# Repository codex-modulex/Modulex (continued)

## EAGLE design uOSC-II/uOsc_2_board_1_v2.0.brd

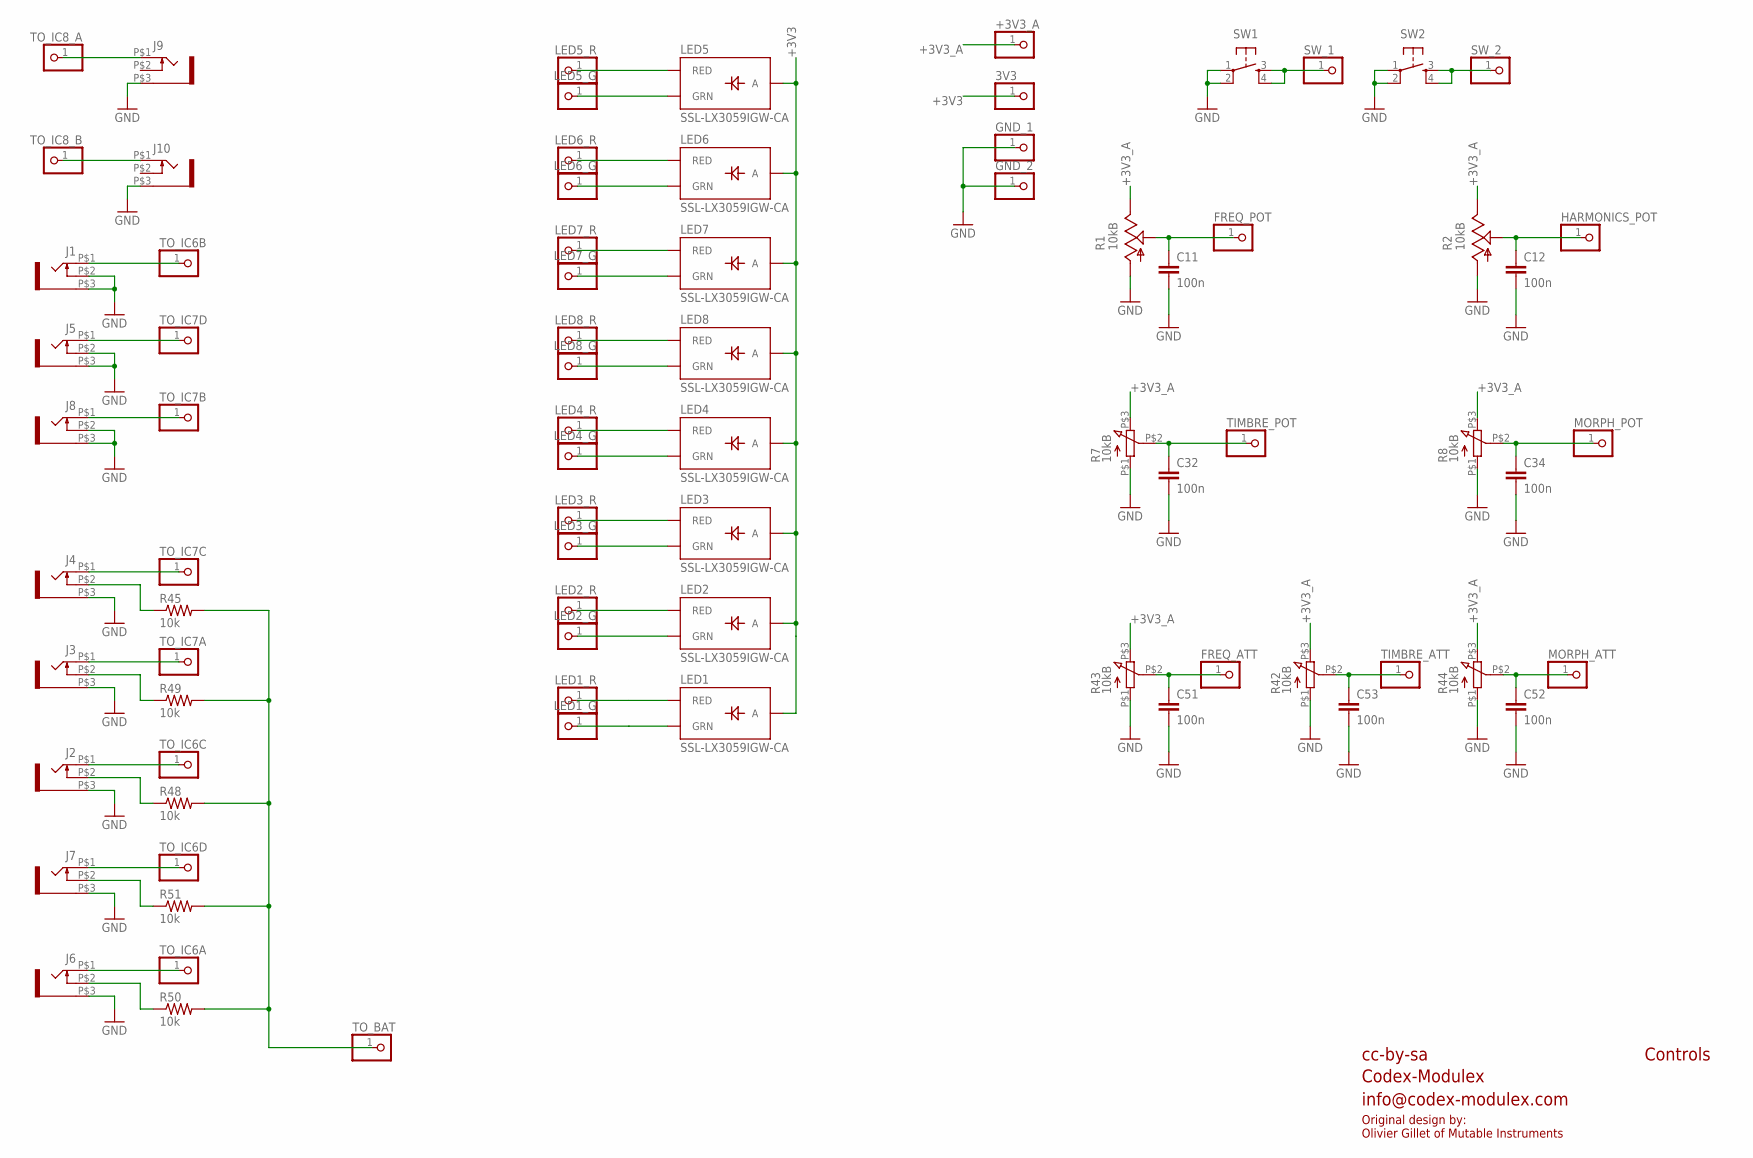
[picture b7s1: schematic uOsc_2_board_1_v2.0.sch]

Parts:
3V3: PARTS_AMAN_PINHD-1X1; PARTS_AMAN_1X01
+3V3_A: PARTS_AMAN_PINHD-1X1; PARTS_AMAN_1X01
C11, C12, C32, C34, C51, C52, C53: 100n; PARTS_AMAN_RESISTOR_0603
FREQ_ATT: PARTS_AMAN_PINHD-1X1; PARTS_AMAN_1X01
FREQ_POT: PARTS_AMAN_PINHD-1X1; PARTS_AMAN_1X01
GND_1, GND_2: PARTS_AMAN_PINHD-1X1; PARTS_AMAN_1X01
HARMONICS_POT: PARTS_AMAN_PINHD-1X1; PARTS_AMAN_1X01
J1, J2, J3, J4, J5, J6, J7, J8, J9, J10: WQP-PJ301M-12_JACK
LED1, LED2, LED3, LED4, LED5, LED6, LED7, LED8: SSL-LX3059IGW-CA; LED-BICOLOR-THROUGHHOLE-LUMEX
LED1_G, LED1_R, LED2_G, LED2_R, LED3_G, LED3_R, LED4_G, LED4_R, LED5_G, LED5_R, LED6_G, LED6_R, LED7_G, LED7_R, LED8_G, LED8_R: PARTS_AMAN_PINHD-1X1; PARTS_AMAN_1X01
MORPH_ATT: PARTS_AMAN_PINHD-1X1; PARTS_AMAN_1X01
MORPH_POT: PARTS_AMAN_PINHD-1X1; PARTS_AMAN_1X01
R1, R2: 10kB; ALPS_POT_VERTICAL_PS
R7, R8, R42, R43, R44: 10kB; INSTRUO_Q-POT2
R45, R48, R49, R50, R51: 10k; PARTS_AMAN_RESISTOR_0603
SW1, SW2: TAC_SWITCHPTH; TACTILE-PTH
SW_1, SW_2: PARTS_AMAN_PINHD-1X1; PARTS_AMAN_1X01
TIMBRE_ATT: PARTS_AMAN_PINHD-1X1; PARTS_AMAN_1X01
TIMBRE_POT: PARTS_AMAN_PINHD-1X1; PARTS_AMAN_1X01
TO_BAT: PARTS_AMAN_PINHD-1X1; PARTS_AMAN_1X01
TO_IC6A, TO_IC6B, TO_IC6C, TO_IC6D, TO_IC7A, TO_IC7B, TO_IC7C, TO_IC7D, TO_IC8_A, TO_IC8_B: PARTS_AMAN_PINHD-1X1; PARTS_AMAN_1X01

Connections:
+3V3: 3V3.1, LED1.A, LED2.A, LED3.A, LED4.A, LED5.A, LED6.A, LED7.A, LED8.A
+3V3_A: +3V3_A.1, R1.P$1 (E), R2.P$1 (E), R7.P$3 (3), R8.P$3 (3), R42.P$3 (3), R43.P$3 (3), R44.P$3 (3)
FREQ_ATT: C51.1, FREQ_ATT.1, R43.P$2 (2)
FREQ_POT: C11.1, FREQ_POT.1, R1.P$2 (S)
GND: C11.2, C12.2, C32.2, C34.2, C51.2, C52.2, C53.2, GND_1.1, GND_2.1, J1.P$2 (3), J1.P$3 (1), J2.P$3 (1), J3.P$3 (1), J4.P$3 (1), J5.P$2 (3), J5.P$3 (1), J6.P$3 (1), J7.P$3 (1), J8.P$2 (3), J8.P$3 (1), J9.P$3 (1), J10.P$3 (1), R1.P$3 (A), R2.P$3 (A), R7.P$1 (1), R8.P$1 (1), R42.P$1 (1), R43.P$1 (1), R44.P$1 (1), SW1.1, SW1.2, SW2.1, SW2.2
HARMONICS_POT: C12.1, HARMONICS_POT.1, R2.P$2 (S)
MORPH_ATT: C52.1, MORPH_ATT.1, R44.P$2 (2)
MORPH_POT: C34.1, MORPH_POT.1, R8.P$2 (2)
unnamed: LED1.GREEN_C (GRN), LED1_G.1
unnamed: LED2.GREEN_C (GRN), LED2_G.1
unnamed: LED2.RED_C (RED), LED2_R.1
unnamed: J4.P$1 (2), TO_IC7C.1
unnamed: LED1.RED_C (RED), LED1_R.1
unnamed: LED3.RED_C (RED), LED3_R.1
unnamed: LED3.GREEN_C (GRN), LED3_G.1
unnamed: LED4.RED_C (RED), LED4_R.1
unnamed: LED4.GREEN_C (GRN), LED4_G.1
unnamed: LED8.RED_C (RED), LED8_R.1
unnamed: LED8.GREEN_C (GRN), LED8_G.1
unnamed: LED7.RED_C (RED), LED7_R.1
unnamed: LED7.GREEN_C (GRN), LED7_G.1
unnamed: J1.P$1 (2), TO_IC6B.1
unnamed: LED6.RED_C (RED), LED6_R.1
unnamed: LED6.GREEN_C (GRN), LED6_G.1
unnamed: LED5.RED_C (RED), LED5_R.1
unnamed: LED5.GREEN_C (GRN), LED5_G.1
unnamed: J9.P$1 (2), TO_IC8_A.1
unnamed: J10.P$1 (2), TO_IC8_B.1
unnamed: J5.P$1 (2), TO_IC7D.1
unnamed: J8.P$1 (2), TO_IC7B.1
unnamed: J3.P$1 (2), TO_IC7A.1
unnamed: J2.P$1 (2), TO_IC6C.1
unnamed: J7.P$1 (2), TO_IC6D.1
unnamed: J6.P$1 (2), TO_IC6A.1
unnamed: J4.P$2 (3), R45.1
unnamed: J3.P$2 (3), R49.1
unnamed: J2.P$2 (3), R48.1
unnamed: J7.P$2 (3), R51.1
unnamed: J6.P$2 (3), R50.1
unnamed: R45.2, R48.2, R49.2, R50.2, R51.2, TO_BAT.1
SW_1: SW1.3, SW1.4, SW_1.1
SW_2: SW2.3, SW2.4, SW_2.1
TIMBRE_ATT: C53.1, R42.P$2 (2), TIMBRE_ATT.1
TIMBRE_POT: C32.1, R7.P$2 (2), TIMBRE_POT.1

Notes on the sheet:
cc-by-sa
Codex-Modulex
info@codex-modulex.com
Controls
Original design by: Olivier Gillet of Mutable Instruments

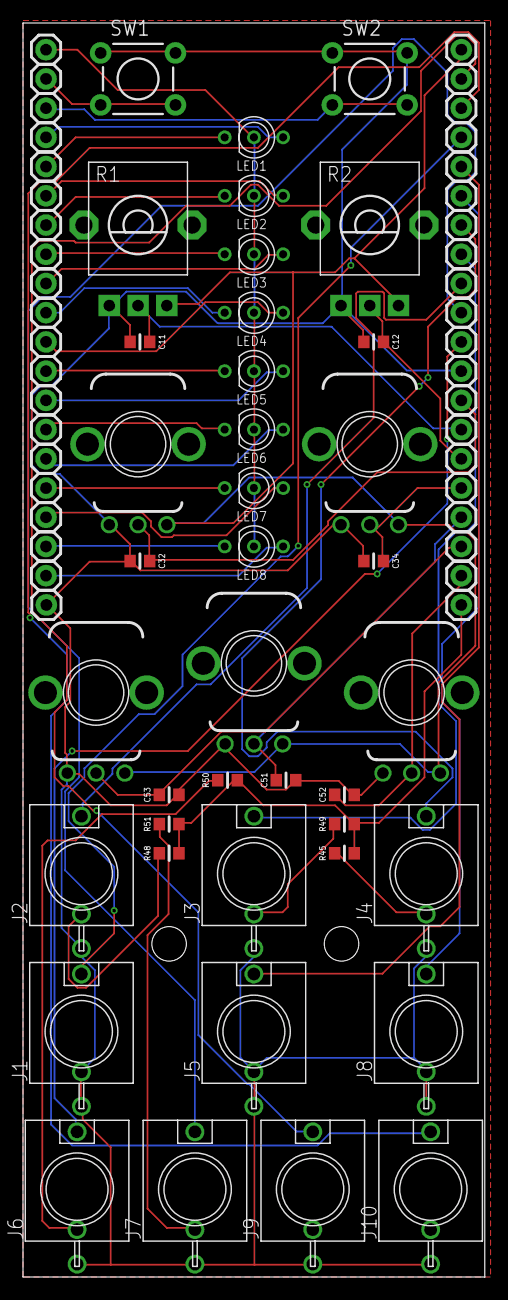
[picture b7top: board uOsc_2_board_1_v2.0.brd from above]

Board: 2 copper layers, 40.1 x 109.0 mm, 79 parts (0 on the bottom side), 44 nets.

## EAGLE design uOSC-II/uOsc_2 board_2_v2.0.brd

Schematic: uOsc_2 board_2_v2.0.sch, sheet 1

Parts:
C9, C19, C24, C25: 1u; PARTS_AMAN_RESISTOR_0603
C10, C15, C20, C23, C26: 100n; PARTS_AMAN_RESISTOR_0603
C14, C21: 20p; PARTS_AMAN_RESISTOR_0603
IC4: STM32F373CCT6; LQFP48
JP5: M02PTH; 1X02
JP6: M04PTH; 1X04
Q1: 8MHz; CTS406
R4: 10k; PARTS_AMAN_RESISTOR_0603
R5, R6, R9, R10: 100; PARTS_AMAN_RESISTOR_0603

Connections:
+3V3: C9.1, C10.1, C25.1, C26.1, IC4.1 (VBAT), IC4.17 (VDD_2), IC4.48 (VDD_1), R4.1; also elsewhere on the board
+3V3_A: C19.1, C20.1, C23.1, C24.1, IC4.9 (VDDA), IC4.24 (VDDSD), IC4.25 (VREFSD+); also elsewhere on the board
ADC_FM: IC4.22 (PE9/SDADC1_AIN7P/SDADC1_AIN8M/SDADC2_AI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); also elsewhere on the board
ADC_GATE: IC4.21 (PE8/SDADC1_AIN8P/SDADC2_AIN8P); also elsewhere on the board
ADC_HARMONICS: IC4.28 (PD8/SPI2_SCK/I2S2_CK/USART3_TX/SDADC3_A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); also elsewhere on the board
ADC_MODEL: IC4.19 (PB1/TIM3_CH4/ADC_IN9/SDADC1_AIN5P/SDADC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); also elsewhere on the board
ADC_MORPH: IC4.27 (PB15/SPI2_MOSI/I2S2_SD/SDADC3_AIN7P/SDA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); also elsewhere on the board
ADC_TIMBRE: IC4.20 (PB2/SDADC1_AIN4P/SDADC2_AIN6P); also elsewhere on the board
ADC_TRIG: IC4.18 (PB0/SPI1_MOSI/I2S1_SD/TIM3_CH3/ADC_IN8/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); also elsewhere on the board
ADC_V_OCT: IC4.26 (PB14/SPI2_MISO/I2S2_MCK/USART3_RTS/SDAD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); also elsewhere on the board
DAC_BCK: IC4.29 (PA8/SPI2_SCK/I2S2_CK/I2C2_SMBA/USART1_C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); also elsewhere on the board
DAC_DIN: IC4.31 (PA10/SPI2_MOSI/I2S2_SD/I2C2_SDA/USART1_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); also elsewhere on the board
DAC_LRCK: IC4.32 (PA11/SPI2_NSS/I2S2_WS/SPI1_NSS/I2S1_WS/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); also elsewhere on the board
FREQ_ATT: IC4.15 (PA5/SPI1_SCK/I2S1_CK/TIM2_CH1/ADC_IN5/D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); also elsewhere on the board
FREQ_POT: IC4.10 (PA0/USART2_CTS/TIM2_CH1/TIM5_CH1/ADC_IN0); also elsewhere on the board
GND: C9.2, C10.2, C14.1, C15.2, C19.2, C20.2, C21.1, C23.2, C24.2, C25.2, C26.2, IC4.8 (VSSA), IC4.23 (VSSSD/VREFSD-), IC4.44 (BOOT0), IC4.47 (VSS_1), JP6.1, Q1.2 (LID1), Q1.4 (LID2); also elsewhere on the board
HARMONICS_POT: IC4.12 (PA2/SPI3_MISO/I2S3_MCK/USART2_TX/TIM2_C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); also elsewhere on the board
LEDS_SCK: IC4.33 (PA12/SPI1_SCK/I2S1_CK/USART1_RTS/CAN_TX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); also elsewhere on the board
LEDS_SIN: IC4.35 (PF6/SPI1_MOSI/I2S1_SD/USART3_RTS/TIM4_C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); also elsewhere on the board
LEDS_SS: IC4.36 (PF7/I2C2_SDA/USART2_CK); also elsewhere on the board
MORPH_ATT: IC4.14 (PA4/SPI1_NSS/I2S1_WS/SPI3_NSS/I2S3_WS/U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); also elsewhere on the board
MORPH_POT: IC4.11 (PA1/SPI3_SCK/I2S3_CK/USART2_RTS/TIM2_CH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); also elsewhere on the board
unnamed: IC4.5 (PF0/OSC_IN/I2C2_SDA), R5.1
unnamed: IC4.6 (PF1/OSC_OUT/I2C2_SCL), R6.1
unnamed: C14.2, Q1.3 (2), R5.2
unnamed: JP5.2, R10.1
unnamed: C21.2, Q1.1, R6.2
unnamed: JP5.1, R9.1
NORMALIZATION_PROBE: IC4.30 (PA9/SPI_MISO/I2S2_MCK/I2C2_SCL/USART1_T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); also elsewhere on the board
RESET: C15.1, IC4.7 (NRST), JP6.4, R4.2
RX: IC4.46 (PB9/SPI2_NSS/I2S2_WS/I2C1_SDA/USART3_RX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), R9.2
SWCLK: IC4.37 (PA14/I2C1_SDA/JTCK-SWCLK), JP6.3
SWDIO: IC4.34 (PA13/SPI1_MISO/I2S1_MCK/USART3_CTS/TIM4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), JP6.2
SW_1: IC4.43 (PB7/I2C1_SDA/USART1_RX/TIM4_CH2); also elsewhere on the board
SW_2: IC4.42 (PB6/I2C1_SCL/USART1_TX/TIM4_CH1); also elsewhere on the board
TIMBRE_ATT: IC4.16 (PA6/SPI1_MISO/I2S1_MCK/TIM3_CH1/ADC_IN6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); also elsewhere on the board
TIMBRE_POT: IC4.13 (PA3/SPI3_MOSI/I2S3_SD/USART2_RX/TIM2_CH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); also elsewhere on the board
TX: IC4.45 (PB8/SPI2_SCK/I2S2_CK/I2C1_SCL/USART3_TX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), R10.2

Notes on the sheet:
cc-by-sa
Codex-Modulex
info@codex-modulex.com
MCU
Factory testing interface
Original design by: Olivier Gillet of Mutable Instruments

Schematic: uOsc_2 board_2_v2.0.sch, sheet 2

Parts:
3V3: PARTS_AMAN_PINHD-1X1; PARTS_AMAN_1X01
+3V3_A: PARTS_AMAN_PINHD-1X1; PARTS_AMAN_1X01
C7: 10u; PANASONIC_A
C8: 100n; PARTS_AMAN_RESISTOR_0603
FREQ_ATT: PARTS_AMAN_PINHD-1X1; PARTS_AMAN_1X01
FREQ_POT: PARTS_AMAN_PINHD-1X1; PARTS_AMAN_1X01
GND_1: GND_1; PARTS_AMAN_1X01
GND_2: GND_2; PARTS_AMAN_1X01
HARMONICS_POT: PARTS_AMAN_PINHD-1X1; PARTS_AMAN_1X01
IC2: TLC59281DBQ; TSSOP24_0635
L4: WE-CBF_0603; 0603
LED1_G, LED1_R, LED2_G, LED2_R, LED3_G, LED3_R, LED4_G, LED4_R, LED5_G, LED5_R, LED6_G, LED6_R, LED7_G, LED7_R, LED8_G, LED8_R: PARTS_AMAN_PINHD-1X1; PARTS_AMAN_1X01
MORPH_ATT: PARTS_AMAN_PINHD-1X1; PARTS_AMAN_1X01
MORPH_POT: PARTS_AMAN_PINHD-1X1; PARTS_AMAN_1X01
R3: 10k; PARTS_AMAN_RESISTOR_0603
SW1, SW2: PARTS_AMAN_PINHD-1X1; PARTS_AMAN_1X01
TIMBRE_ATT: PARTS_AMAN_PINHD-1X1; PARTS_AMAN_1X01
TIMBRE_POT: PARTS_AMAN_PINHD-1X1; PARTS_AMAN_1X01

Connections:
+3V3: 3V3.1, L4.2; also elsewhere on the board
+3V3_A: +3V3_A.1; also elsewhere on the board
FREQ_ATT: FREQ_ATT.1; also elsewhere on the board
FREQ_POT: FREQ_POT.1; also elsewhere on the board
GND: C7.-, C8.2, GND_1.1, GND_2.1, IC2.1 (GND), IC2.21 (BLANK), R3.2; also elsewhere on the board
HARMONICS_POT: HARMONICS_POT.1; also elsewhere on the board
LEDS_SCK: IC2.3 (SCLK); also elsewhere on the board
LEDS_SIN: IC2.2 (SIN); also elsewhere on the board
LEDS_SS: IC2.4 (LAT); also elsewhere on the board
MORPH_ATT: MORPH_ATT.1; also elsewhere on the board
MORPH_POT: MORPH_POT.1; also elsewhere on the board
unnamed: IC2.12 (OUT7), LED8_G.1
unnamed: IC2.11 (OUT6), LED8_R.1
unnamed: IC2.10 (OUT5), LED7_G.1
unnamed: IC2.9 (OUT4), LED7_R.1
unnamed: IC2.8 (OUT3), LED6_G.1
unnamed: IC2.13 (OUT8), LED4_R.1
unnamed: IC2.7 (OUT2), LED6_R.1
unnamed: IC2.14 (OUT9), LED4_G.1
unnamed: IC2.6 (OUT1), LED5_G.1
unnamed: IC2.15 (OUT10), LED3_R.1
unnamed: IC2.16 (OUT11), LED3_G.1
unnamed: IC2.17 (OUT12), LED2_R.1
unnamed: IC2.18 (OUT13), LED2_G.1
unnamed: IC2.19 (OUT14), LED1_R.1
unnamed: IC2.5 (OUT0), LED5_R.1
unnamed: IC2.20 (OUT15), LED1_G.1
unnamed: C7.+, C8.1, IC2.24 (VCC), L4.1
unnamed: IC2.23 (IREF), R3.1
SW_1: SW1.1; also elsewhere on the board
SW_2: SW2.1; also elsewhere on the board
TIMBRE_ATT: TIMBRE_ATT.1; also elsewhere on the board
TIMBRE_POT: TIMBRE_POT.1; also elsewhere on the board

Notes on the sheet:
cc-by-sa
Codex-Modulex
info@codex-modulex.com
Controls
Original design by: Olivier Gillet of Mutable Instruments

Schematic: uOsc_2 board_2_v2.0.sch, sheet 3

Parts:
C36, C44: 100n; PARTS_AMAN_RESISTOR_0603
C38, C46: 100p; PARTS_AMAN_RESISTOR_0603
C39, C40, C41, C47, C48, C49: 1.0n; PARTS_AMAN_RESISTOR_0603
C54, C55, C56, C57, C58, C59, C60, C61: ESD; PARTS_AMAN_RESISTOR_0603
D3: BAT54S; SOT23
IC6, IC7: MCP6004; TSSOP14_065
R13, R14, R15, R24, R38, R39, R40, R41: 100k; PARTS_AMAN_RESISTOR_0603
R17: 56k; PARTS_AMAN_RESISTOR_0603
R18, R20, R31, R34: 33k; PARTS_AMAN_RESISTOR_0603
R19, R32, R35: 20k; PARTS_AMAN_RESISTOR_0603
R23, R33, R36: 120k; PARTS_AMAN_RESISTOR_0603
R25, R27, R30: 200k; PARTS_AMAN_RESISTOR_0603
R26: 110k; PARTS_AMAN_RESISTOR_0603
R29: 140k; PARTS_AMAN_RESISTOR_0603
TO_BAT: PARTS_AMAN_PINHD-1X1; PARTS_AMAN_1X01
TO_IC6A, TO_IC6B, TO_IC6C, TO_IC6D, TO_IC7A, TO_IC7B, TO_IC7C, TO_IC7D: PARTS_AMAN_PINHD-1X1; PARTS_AMAN_1X01

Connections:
+3V3: D3.2 (C); also elsewhere on the board
+3V3_A: C36.1, C44.1, IC6.4 (V+), IC7.4 (V+); also elsewhere on the board
ADC_FM: C40.2, IC7.1 (OUT), R19.1; also elsewhere on the board
ADC_GATE: C39.2, IC6.14 (OUT), R18.1; also elsewhere on the board
ADC_HARMONICS: C41.2, IC7.14 (OUT), R20.1; also elsewhere on the board
ADC_MODEL: C46.2, IC6.7 (OUT), R31.1; also elsewhere on the board
ADC_MORPH: C49.2, IC7.8 (OUT), R35.1; also elsewhere on the board
ADC_TIMBRE: C47.2, IC6.8 (OUT), R32.1; also elsewhere on the board
ADC_TRIG: C38.2, IC6.1 (OUT), R17.1; also elsewhere on the board
ADC_V_OCT: C48.2, IC7.7 (OUT), R34.1; also elsewhere on the board
AREF_-10: R23.2, R25.2, R26.2, R27.2, R29.2, R30.2, R33.2, R36.2; also elsewhere on the board
FM_IN: C57.1, R15.2, TO_IC7A.1
GATE_IN: C61.1, R14.2, TO_IC6D.1
GATE_IN1: C59.1, R24.2, TO_IC6A.1
GND: C36.2, C44.2, C54.2, C55.2, C56.2, C57.2, C58.2, C59.2, C60.2, C61.2, D3.1 (A), IC6.3 (+IN), IC6.5 (+IN), IC6.10 (+IN), IC6.11 (V-), IC6.12 (+IN), IC7.3 (+IN), IC7.5 (+IN), IC7.10 (+IN), IC7.11 (V-), IC7.12 (+IN); also elsewhere on the board
HARMONICS_IN: C58.1, R13.2, TO_IC7D.1
MODEL_IN: C55.1, R40.2, TO_IC6B.1
MORPH_IN: C54.1, R39.2, TO_IC7C.1
unnamed: C38.1, IC6.2 (-IN), R17.2, R24.1, R25.1
unnamed: C39.1, IC6.13 (-IN), R14.1, R18.2, R26.1
unnamed: C48.1, IC7.6 (-IN), R29.1, R34.2, R38.1
unnamed: C56.1, R41.2, TO_IC6C.1
unnamed: C49.1, IC7.9 (-IN), R35.2, R36.1, R39.1
unnamed: C40.1, IC7.2 (-IN), R15.1, R19.2, R23.1
unnamed: C46.1, IC6.6 (-IN), R30.1, R31.2, R40.1
unnamed: C47.1, IC6.9 (-IN), R32.2, R33.1, R41.1
unnamed: C41.1, IC7.13 (-IN), R13.1, R20.2, R27.1
NORMALIZATION_PROBE: D3.3 (AC), TO_BAT.1; also elsewhere on the board
V_OCT_IN: C60.1, R38.2, TO_IC7B.1

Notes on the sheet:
cc-by-sa
Codex-Modulex
info@codex-modulex.com
CV inputs
-3.0V to 7.0V
-8.0V to 8.0V
-5.0V to 5.0V
-0.8V to 8.0V
-0.8V to 5.0V
Optional ESD protection:
1.0nF capacitor
or:
Ceradiode (eg TDK B72500D160H60, AEM ES0603V014CT)
Original design by: Olivier Gillet of Mutable Instruments

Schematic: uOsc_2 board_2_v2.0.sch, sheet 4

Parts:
C16, C30: 10u; PANASONIC_A
C17, C18, C27, C28, C37, C45: 100n; PARTS_AMAN_RESISTOR_0603
C29, C31: 2.2u; C0805
C33, C35: 1.0n; PARTS_AMAN_RESISTOR_0603
C42, C43: 100p; PARTS_AMAN_RESISTOR_0603
IC5: PCM5100APW; SSOP20
IC8: TL072PW; TSSOP08
R11, R12: 2.2k; PARTS_AMAN_RESISTOR_0603
R16, R21: 10k; PARTS_AMAN_RESISTOR_0603
R22, R28: 33k; PARTS_AMAN_RESISTOR_0603
R46, R47: 1.0k; PARTS_AMAN_RESISTOR_0603
TO_IC8A, TO_IC8B: PARTS_AMAN_PINHD-1X1; PARTS_AMAN_1X01

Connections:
+3V3: C16.+, C17.1, IC5.11 (FLT), IC5.17 (XSMT), IC5.20 (DVDD); also elsewhere on the board
+3V3_A: C27.1, C28.1, C30.+, IC5.1 (CPVDD), IC5.8 (AVDD); also elsewhere on the board
DAC_BCK: IC5.13 (BCK); also elsewhere on the board
DAC_DIN: IC5.14 (DIN); also elsewhere on the board
DAC_LRCK: IC5.15 (LRCK); also elsewhere on the board
GND: C16.-, C17.2, C18.2, C27.2, C28.2, C30.-, C31.2, C33.2, C35.2, C37.2, C45.1, IC5.3 (CPGND), IC5.9 (AGND), IC5.10 (DEMP), IC5.12 (SCK), IC5.16 (FMT), IC5.19 (DGND), IC8.3 (+IN), IC8.5 (+IN); also elsewhere on the board
unnamed: C29.1, IC5.2 (CAPP)
unnamed: C29.2, IC5.4 (CAPM)
unnamed: IC5.6 (OUTL), R11.2
unnamed: C33.1, R11.1, R21.2
unnamed: C35.1, R12.1, R16.2
unnamed: C31.1, IC5.5 (VNEG)
unnamed: C18.1, IC5.18 (LDOO)
unnamed: IC5.7 (OUTR), R12.2
unnamed: C43.1, IC8.6 (-IN), R16.1, R28.2
unnamed: C43.2, IC8.7 (OUT), R28.1, R47.2
unnamed: C42.1, IC8.2 (-IN), R21.1, R22.2
unnamed: C42.2, IC8.1 (OUT), R22.1, R46.2
unnamed: R46.1, TO_IC8A.1
unnamed: R47.1, TO_IC8B.1
VCC: C37.1, IC8.8 (V+); also elsewhere on the board
VEE: C45.2, IC8.4 (V-); also elsewhere on the board

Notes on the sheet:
cc-by-sa
Codex-Modulex
info@codex-modulex.com
DAC and outputs
Original design by: Olivier Gillet of Mutable Instruments

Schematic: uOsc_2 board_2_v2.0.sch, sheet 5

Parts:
C1, C2, C13: 22u; C1206
C3, C22: 10u; PANASONIC_A
C4, C5: 22u; PANASONIC_B
C6: 100n; PARTS_AMAN_RESISTOR_0603
C50: 1u; PARTS_AMAN_RESISTOR_0603
D1, D2: 1N5819HW; SOD123
IC1: R-78E3.3-0.5; WE78
IC3: LD2981ABU33; SOT89
IC9: LM4040B10; DBZ_R-PDSO-G3
JP8: M05X2SHD; 2X5-SHROUDED
L1: 33u; L2012C
L2, L3, L5: WE-CBF_0603; 0603
R37: 2.2k; PARTS_AMAN_RESISTOR_0603

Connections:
+3V3: C3.+, C6.1, IC1.3 (VO); also elsewhere on the board
+3V3_A: C22.+, IC3.1 (VO); also elsewhere on the board
AREF_-10: C50.1, IC9.2 (A), R37.2; also elsewhere on the board
GND: C1.2, C2.2, C3.-, C4.-, C5.+, C6.2, C13.2, C22.-, C50.2, IC1.2 (GND), IC3.2 (GND), IC9.1 (C), JP8.3, JP8.4, JP8.5, JP8.6, JP8.7, JP8.8; also elsewhere on the board
unnamed: C1.1, IC1.1 (VI), L1.2
unnamed: D2.A, L3.2
unnamed: C2.1, D1.C, L1.1, L2.2, L5.2
unnamed: C13.1, IC3.3 (VI), L5.1
unnamed: D1.A, JP8.9, JP8.10
unnamed: D2.C, JP8.1, JP8.2
VCC: C4.+, L2.1; also elsewhere on the board
VEE: C5.-, L3.1, R37.1; also elsewhere on the board

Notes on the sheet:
cc-by-sa
Codex-Modulex
info@codex-modulex.com
Power
0.56mA needed
Wurth 742792664
0.68mA delivered
Original design by: Olivier Gillet of Mutable Instruments

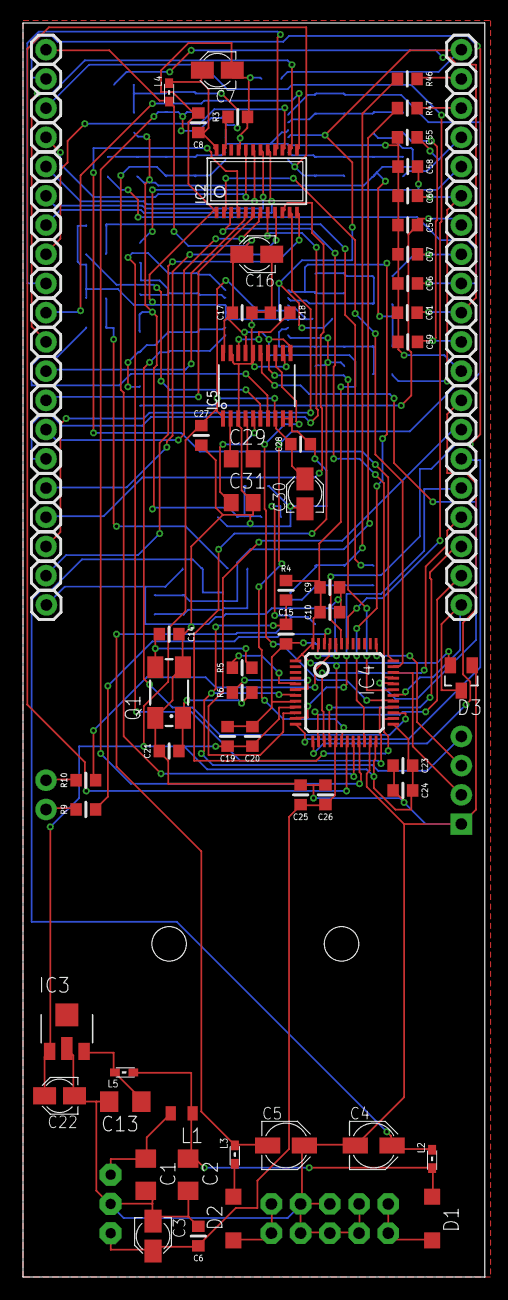
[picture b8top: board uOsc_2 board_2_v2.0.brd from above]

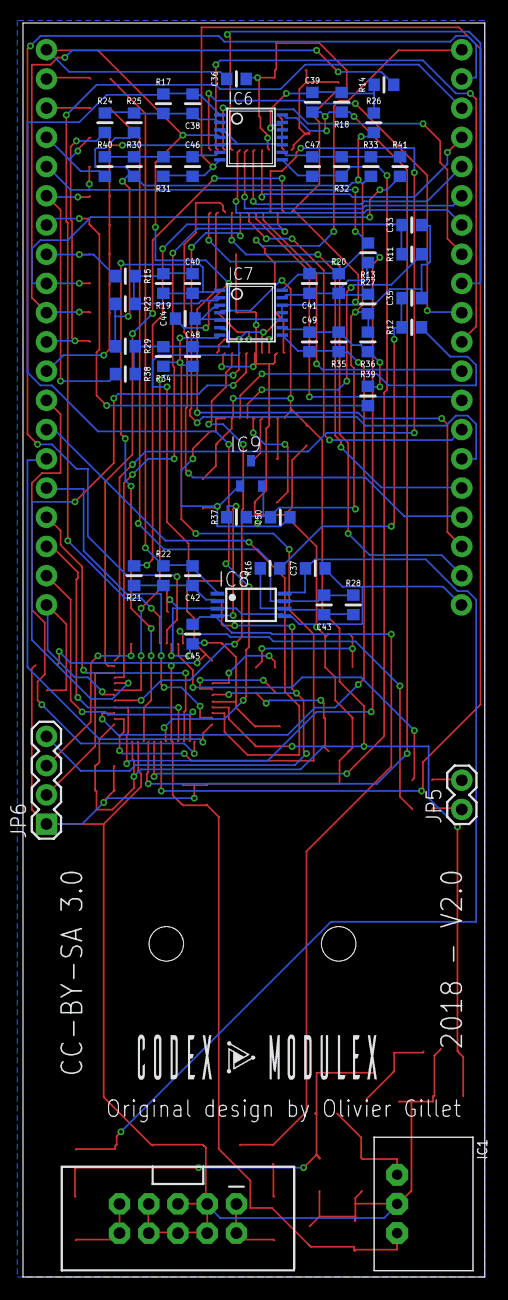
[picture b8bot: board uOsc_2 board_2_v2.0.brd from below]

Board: 2 copper layers, 40.1 x 109.0 mm, 155 parts (57 on the bottom side), 95 nets.

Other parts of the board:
U$1: GMSN_LMNC_LOGO

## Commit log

2021-11-08 u4xVCA
2021-11-08 uNimbus
2021-11-08 various uploads
2021-12-04 last version uRinks
2022-01-10 some versions of uSlices
